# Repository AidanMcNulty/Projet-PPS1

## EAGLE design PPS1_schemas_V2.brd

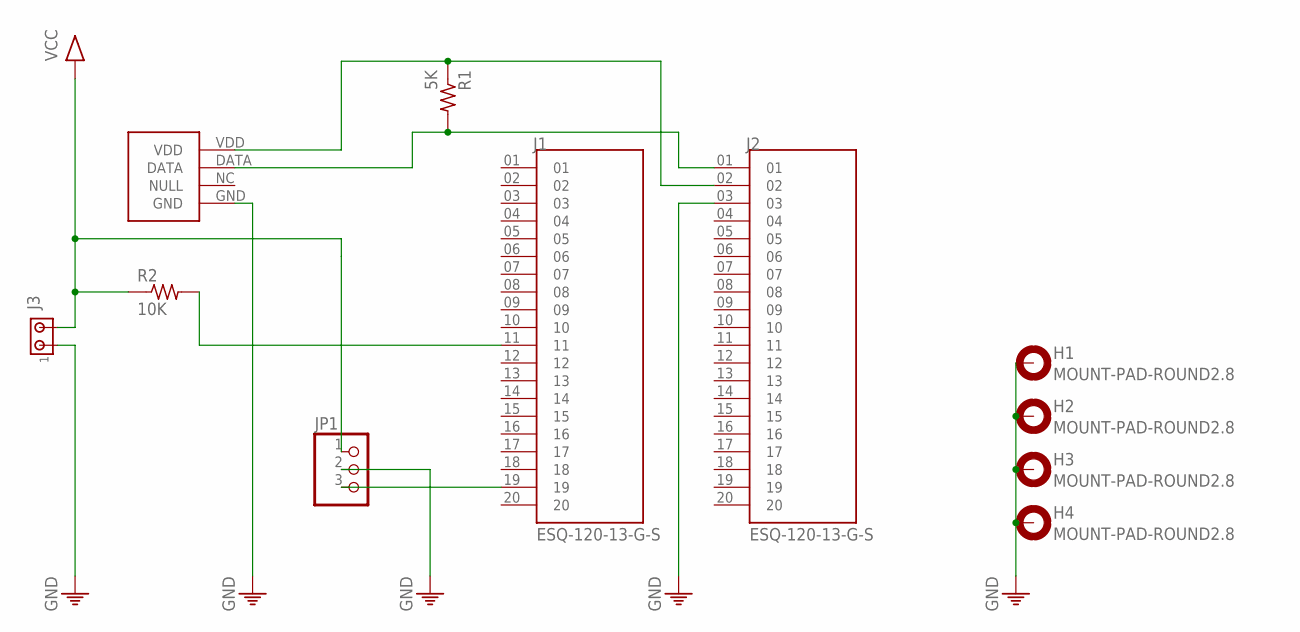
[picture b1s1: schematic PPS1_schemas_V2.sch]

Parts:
H1, H2, H3, H4: MOUNT-PAD-ROUND2.8; 2,8-PAD
J1, J2: ESQ-120-13-G-S; SAMTEC_ESQ-120-13-G-S
J3: MTA02-100; 10X02MTA
JP1: PINHD-1X3; 1X03
R1: 5K; M1206
R2: 10K; M1206
U$1: DHT22

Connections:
unnamed: J2.01, R1.2, U$1.DATA
unnamed: J2.02, R1.1, U$1.VDD
unnamed: J1.11, R2.2
unnamed: J1.19, JP1.3
PE: H1.B2,8, H2.B2,8, H3.B2,8, H4.B2,8, J1.18, J2.03, J3.1, JP1.2, U$1.GND
VCC: J3.2, JP1.1, R2.1

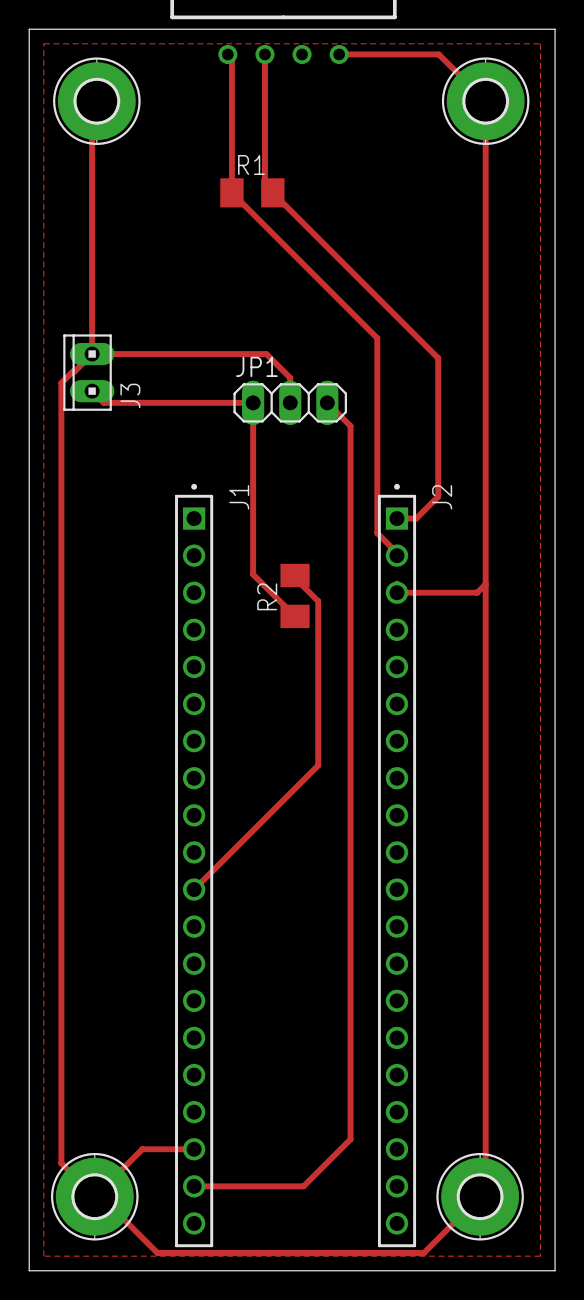
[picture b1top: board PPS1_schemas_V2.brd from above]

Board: 2 copper layers, 36.0 x 85.0 mm, 11 parts (0 on the bottom side), 6 nets.

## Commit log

2024-10-24 Add files via upload
    Diagramme schématique
2024-10-24 Add files via upload
    Diagramme fonctionnelle
2024-10-24 Add files via upload
    Diagramme matricielle
